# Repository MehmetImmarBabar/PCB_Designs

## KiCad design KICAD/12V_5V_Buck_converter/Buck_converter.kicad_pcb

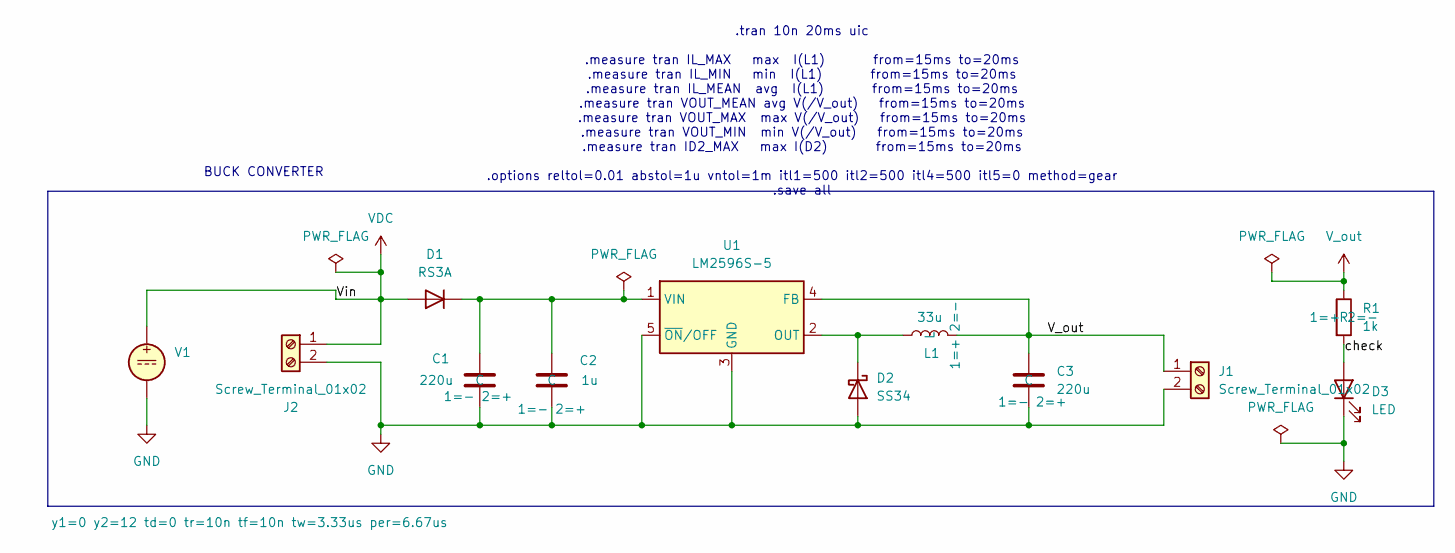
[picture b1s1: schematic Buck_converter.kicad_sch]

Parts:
C1, C3: 220u; C_0201_0603Metric
C2: 1u; C_0201_0603Metric
D1: RS3A; D_MELF
D2: SS34; D_SMA
D3: LED; LED_D5.0mm_Horizontal_O1.27mm_Z3.0mm_Clear
J1, J2: Screw_Terminal_01x02; TerminalBlock_Phoenix_MKDS-1,5-2_1x02_P5.00mm_Horizontal
L1: 33u; L_Coilcraft_MOS6020-XXX
R1: 1k; R_0815_2038Metric
U1: LM2596S-5; TO-263-5_TabPin3
V1: y1=0 y2=12 td=0 tr=10n tf=10n tw=3.33us per=6.67us

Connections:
/check: D3.2 (A), R1.2
GND: C1.2, C2.2, C3.2, D2.2 (A), D3.1 (K), J1.2, J2.2, U1.3 (GND), U1.5 (~ON/OFF), V1.2
unnamed: C1.1, C2.1, D1.1 (K), U1.1 (VIN)
unnamed: D2.1 (K), L1.1, U1.2 (OUT)
VDC: D1.2 (A), J2.1, V1.1
V_out: C3.1, J1.1, L1.2, R1.1, U1.4 (FB)

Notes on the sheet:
.tran 10n 20ms uic .measure tran IL_MAX max I(L1) from=15ms to=20ms .measure tran IL_MIN min I(L1) from=15ms to=20ms .measure tran IL_MEAN avg I(L1) from=15ms to=20ms .measure tran VOUT_MEAN avg V(/V_out) from=15ms to=20ms .measure tran VOUT_MAX max V(/V_out) from=15ms to=20ms .measure tran VOUT_MI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
BUCK CONVERTER

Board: 2 copper layers, 11 parts (0 on the bottom side), 6 nets, no tracks yet.

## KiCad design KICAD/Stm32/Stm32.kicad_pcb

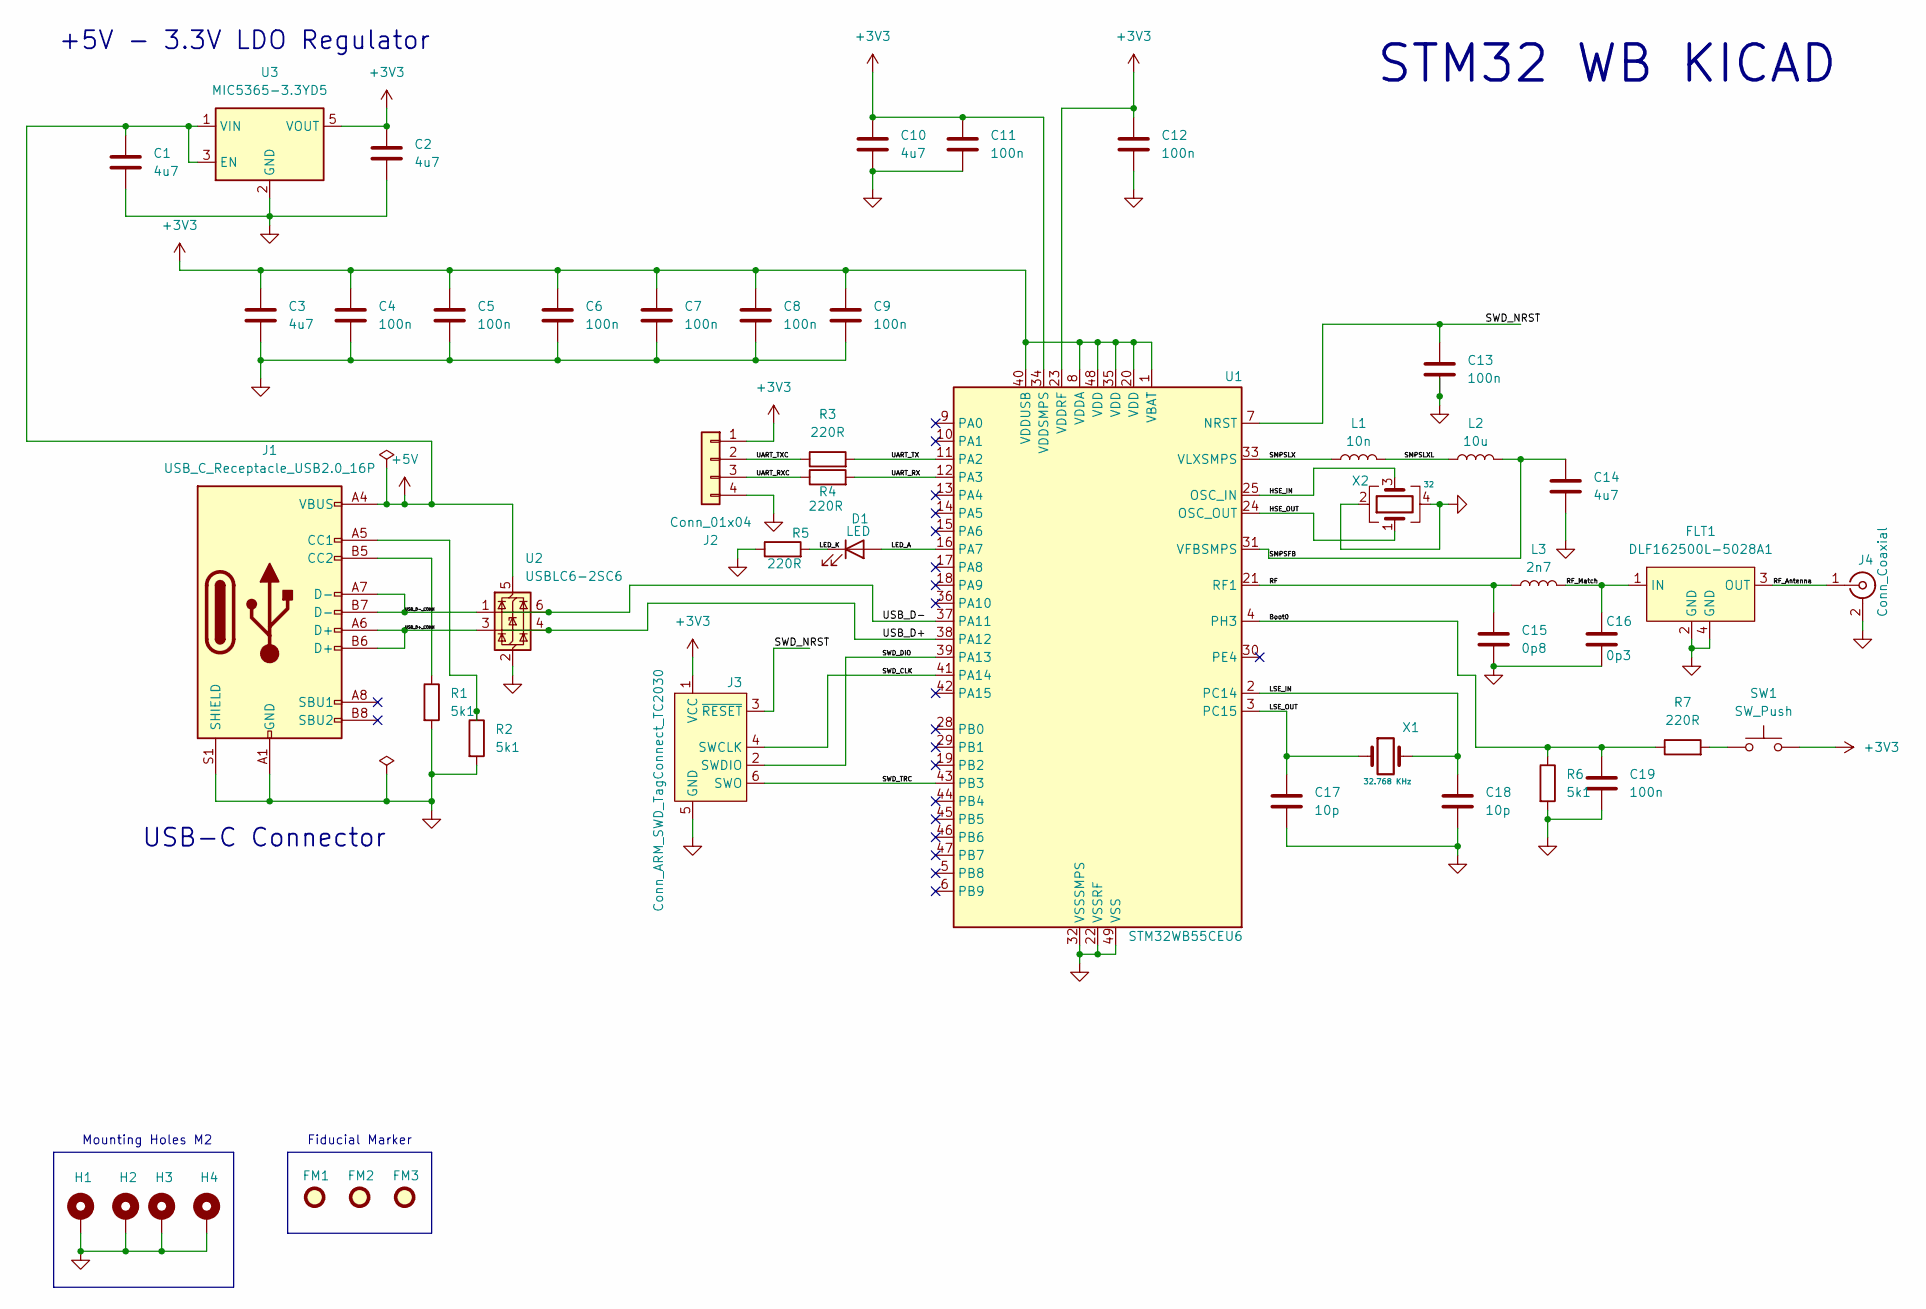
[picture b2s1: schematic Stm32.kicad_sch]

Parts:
C1, C2, C3, C10, C14: 4u7; C_0603_1608Metric
C4, C5, C6, C7, C8, C9, C11, C12, C13, C19: 100n; C_0402_1005Metric
C15: 0p8; C_0402_1005Metric
C16: 0p3; C_0402_1005Metric
C17, C18: 10p; C_0402_1005Metric
D1: LED; LED_0402_1005Metric
FLT1: DLF162500L-5028A1; Untitled_1
FM1, FM2, FM3: Fiducial; Fiducial_1mm_Mask2mm
H1, H2, H3, H4: MountingHole_Pad; MountingHole_2.2mm_M2_Pad_Via
J1: USB_C_Receptacle_USB2.0_16P; USB_C_Receptacle_GCT_USB4105-xx-A_16P_TopMnt_Horizontal
J2: Conn_01x04; Molex_PicoBlade_53048-0410_1x04_P1.25mm_Horizontal
J3: Conn_ARM_SWD_TagConnect_TC2030; Tag-Connect_TC2030-IDC-FP_2x03_P1.27mm_Vertical
J4: Conn_Coaxial; U.FL_Hirose_U.FL-R-SMT-1_Vertical
L1: 10n; L_0402_1005Metric
L2: 10u; L_0805_2012Metric
L3: 2n7; L_0402_1005Metric
R1, R2, R6: 5k1; R_0402_1005Metric
R3, R4, R5, R7: 220R; R_0402_1005Metric
SW1: SW_Push; SW_SPST_CK_RS282G05A3
U1: STM32WB55CEU6; QFN-48-1EP_7x7mm_P0.5mm_EP5.6x5.6mm
U2: USBLC6-2SC6; SOT-23-6
U3: MIC5365-3.3YD5; TSOT-23-5
X1: 32.768 KHz; Crystal_SMD_2012-2Pin_2.0x1.2mm
X2: 32; Crystal_SMD_2016-4Pin_2.0x1.6mm

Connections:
+3V3: C2.1, C3.1, C4.1, C5.1, C6.1, C7.1, C8.1, C9.1, C10.1, C11.1, C12.1, J2.1, J3.1 (VCC), SW1.2, U1.1 (VBAT), U1.8 (VDDA), U1.20 (VDD), U1.23 (VDDRF), U1.34 (VDDSMPS), U1.35 (VDD), U1.40 (VDDUSB), U1.48 (VDD), U3.5 (VOUT)
+5V: C1.1, J1.A4 (VBUS), J1.A9 (VBUS), J1.B4 (VBUS), J1.B9 (VBUS), U2.5 (VBUS), U3.1 (VIN), U3.3 (EN)
/Boot0: C19.1, R6.1, R7.1, U1.4 (PH3)
/HSE_IN: U1.25 (OSC_IN), X2.3
/HSE_OUT: U1.24 (OSC_OUT), X2.1
/LED_A: D1.2 (A), U1.16 (PA7)
/LED_K: D1.1 (K), R5.2
/LSE_IN: C18.1, U1.2 (PC14), X1.2
/LSE_OUT: C17.1, U1.3 (PC15), X1.1
/RF: C15.1, L3.1, U1.21 (RF1)
/RF_Antenna: FLT1.3 (OUT), J4.1 (In)
/RF_Match: C16.1, FLT1.1 (IN), L3.2
/SMPSFB: C14.1, L2.2, U1.31 (VFBSMPS)
/SMPSLX: L1.1, U1.33 (VLXSMPS)
/SMPSLXL: L1.2, L2.1
/SWD_CLK: J3.4 (SWCLK), U1.41 (PA14)
/SWD_DIO: J3.2 (SWDIO), U1.39 (PA13)
/SWD_NRST: C13.1, J3.3 (~RESET), U1.7 (NRST)
/SWD_TRC: J3.6 (SWO), U1.43 (PB3)
/UART_RX: R4.2, U1.12 (PA3)
/UART_RXC: J2.3, R4.1
/UART_TX: R3.2, U1.11 (PA2)
/UART_TXC: J2.2, R3.1
/USB_D+: U1.38 (PA12), U2.4 (I/O2)
/USB_D+_CONN: J1.A6 (D+), J1.B6 (D+), U2.3 (I/O2)
/USB_D-: U1.37 (PA11), U2.6 (I/O1)
/USB_D-_CONN: J1.A7 (D-), J1.B7 (D-), U2.1 (I/O1)
GND: C1.2, C2.2, C3.2, C4.2, C5.2, C6.2, C7.2, C8.2, C9.2, C10.2, C11.2, C12.2, C13.2, C14.2, C15.2, C16.2, C17.2, C18.2, C19.2, FLT1.2 (GND), FLT1.4 (GND), H1.1, H2.1, H3.1, H4.1, J1.A1 (GND), J1.A12 (GND), J1.B1 (GND), J1.B12 (GND), J1.S1 (SHIELD), J2.4, J3.5 (GND), J4.2 (Ext), R1.2, R2.2, R5.1, R6.2, U1.22 (VSSRF), U1.32 (VSSSMPS), U1.49 (VSS), U2.2 (GND), U3.2 (GND), X2.2, X2.4
unnamed: J1.A5 (CC1), R2.1
unnamed: J1.B5 (CC2), R1.1
unnamed: R7.2, SW1.1

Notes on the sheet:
+5V - 3.3V LDO Regulator
USB-C Connector
Mounting Holes M2
STM32 WB KICAD
Fiducial Marker

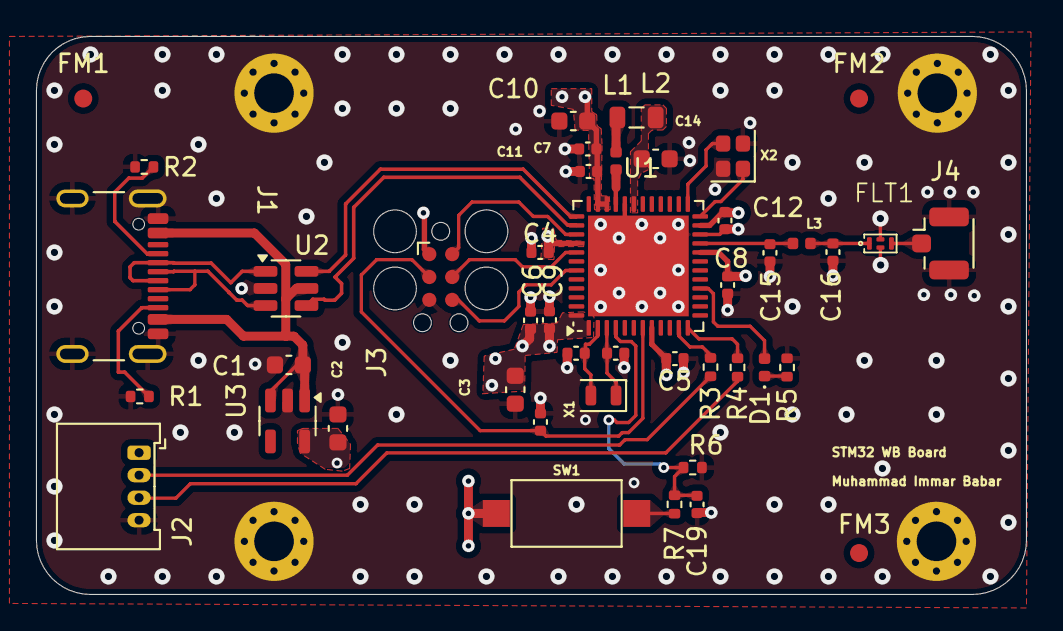
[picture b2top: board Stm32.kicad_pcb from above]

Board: 4 copper layers, 55.0 x 31.0 mm, 48 parts (0 on the bottom side), 31 nets.
